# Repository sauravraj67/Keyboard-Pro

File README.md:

# Keyboard Pro

I built a 65% layout keyboard based on Seed Studio Xiao nrf52840 also It will have a 3.7v battery and an 0.91 inch OLED Screen. Switches will be HotSwapable. I used expander to connect the rows and coluns because there weren't enough pins available.  It is Bluetooth enabled  

## Features
-  nrf52840 Rp2040
- uses 65% Keyboard Layout 
-  Uses Keyboard Matrix
-  Had a rotor encoder and an 0.91 inch oled screen

  | Item | Price | Source |
|------|------:|--------|
| PCB + Shipping - Coupons | 25.14 | JLCPCB |
| KeyCaps | 15.04 | https://meckeys.com/shop/accessories/keyboard-accessories/keycaps/gengar-anime-keycap-set/ |
| Hot-swap (pack of 10) × 7 | 5.50 | https://meckeys.com/shop/accessories/keyboard-accessories/key-switches/kailh-hot-swap-socket/?attribute_pa_variations=white |
| Switches (pack of 10) × 7 | 22.10 | https://meckeys.com/shop/accessories/keyboard-accessories/key-switches/hmx-xinhai-switch/?attribute_pa_key-switches=hmx-xinhai-45g |
| Stabilizers | 10.76 | https://meckeys.com/shop/accessories/keyboard-accessories/more/glorious-goat-stabilizers/ |
| Meckeys Shipping | 1.10 | https://meckeys.com |
| Expander × 2 | 6.22 | https://robu.in/product/pca9555dwr-texas-instruments-400khz-soic-24-300mil-i-o-expanders-rohs/ |
| XIAO BLE nRF52840 | 12.40 | https://robu.in/product/seeed-studio-xiao-ble-nrf52840/ |
| On-Off Switch | 1.12 | https://robu.in/product/os202011ma0qn1-ck-100ma-dpdt-12v-10000-times-plugin-slide-switches-rohs/ |
| 2MΩ Resistor | 0.13 | https://robu.in/product/crcw12062m20fkea-vishay-smd-chip-resistor-2-2-mohm-%c2%b1-1-250-mw-1206-3216-metric-thick-film-general-purpose/ |
| 806kΩ Resistor | 0.13 | https://robu.in/product/rc0402fr-07806kl-yageo-smd-chip-resistor-806-kohm-%c2%b1-1-63-mw-0402-1005-metric-thick-film-general-purpose/ |
| Robu Shipping | 1.10 | https://robu.in |
| Solder Paste for SMD Components | 2.70 | https://www.amazon.in/gp/product/B0GY879KCL/ |
| 1N4148W-T4 Diodes (Pack of 15) × 5 ( used amazon beacuse wasn't avilable anywhere else)| 11.78 | https://www.amazon.in/gp/product/B0FZL2D1GG/ |
| **Total** | **115.22** | |

### Schematic<br><br>

## Made the Key-Matrix 
Hours- 5.5 hr <br>
So I opened the schematics and added a key switch and a diode. Then I had my way toward how many switches would be there per row . The number of keys per row wasn't constant So I made a rough sketch about how would I assign the columns and rows to each Key switch. after that as I would be using keyboard matrix ,so I needed to add a diode to each key switch to prevent ghosting. Then I started making the switch layout . I also kept in mind that each switches aren't of same length so I had to use specific footprints for each switches specifically as per the 65 % standard layout. The Switches will be hot-swapable as well. While making the switch matrix it was a bit time consuming as I tried to organized the switches as well as per there layout ,so that it will be easy for me to connect the wires.While reviewing I found a few placement and footprint mistakes so I solved them then I moved toward making the rows and columns connection and adding the labels to them So this is how it looks.

<br>

## Adding other components

Hours :- 2.5 hr <br>
So there is no footprint and symbol for the Xioa nRF52840 , So I downloaded them and added it to kicad also I knew that there weren't enough numbers of gpio pins on the Xiao nRF52840 so handle all the 15 columns and 5 rows So I needed to use an expander , So for that I used PCA9555D and read it's data sheet a bit , It will communicate to the MCU via I2C protocol , So I started adding the rows and columns label to it but even one expander wasn't enough So I had to add a second one to add the connections of all rows and columns then I did all the other connection on the expander.after that I added pins for Battery connection. the battery that we would be using will be of 3.7v lithium ion battery. and made a battery sense circuit. the nRF52840 has inbuild battery charging IC and it can control the charring part so I don't to add anything more after that I added a 4 pins for 0.91 inch oled display and added labels to it.after that I connected every label to the Xiao nRF52840. So this is how the final schematics look

###  PCB Design<br><br>

## Started with PCB ( Component placement)
Hours :- 4.75 hours <br>
SO I started with the hard part. Arranging the switches . I used a Grid of 19.05U so that the switches snap easily but that wasn't the case . I tried to snap them with each other via using different grid sizes and moving them then they use to snap properly. It look me a long time snapping the switches and overt to that placing switches at the right Place because each rows doesn't have same number of rows I had to align the first switch to the right place , also I added Stabilizers for any switch whose footprint was over 2.25U. The main thing was choosing the right Switch while placing and the most hectic thing was that switches don't use to snap directly . I have to move it around using different grid sizes to achieve the goal . Then I added the Xiao nRF52840 to the right top side a bit away from the corner then added the switches after that placed the Oled screen in the free space and added the expanders in places where there was free space I made few alteration of the keyboard but finally ended up with this after that I placed the diodes near to each respective switch to which it was attached onto the bottom layer of the PCB then I added the boundaries and this is how PCB layout looks now.

 ## Routed the PCB 
 Hours :- 6.5 <br>

 So I stated with routing the PCB I initially routed the diodes to the switches then I moved and started making rows and columns . I tried to make as clean routs as possible then I started routing the rows and columns to the expander . I used vias where there weren't space to rout . I had to make few alteration while routing so that my routs looks clean and workable . Many a times there weren't a way to rout . So I had to re-rout few traces but I was able to rout it to the two expanders. Then I stared connecting the SDA/SCL lines to the MCU from the expander and the OLED screen after that I made connection for the battery pins and battery connected circuit. So after all the rout the PCB looks like this with all the clean straight routs .

###  Made and Polished the Case <br><br>
Hours :- 5.75 hours 

So I took the measurements of the keyboard then made a sketch of same size.after that I added 1 mm releat from each side and added a boundary sketch and curved it edges.after that I need to add sketches for holding the plates . So I added it's boundary and started making symmetric Rectangles and circles for holding the Plate boundary , I repeted it for the tob and bottom<br>then to the sides<br> <br>after that I made a simple base then extruded it as per the needs to make the base Case basic design all the meserments were pre calculated.
after that I added PCB aligned it perfectly with the sketch then moved it to a calculated height ( this time the calculations things were right).then I added the 3D model of the MCU and started making holes on the Case for the USB-C for that I used a simple sketch and extruded to to make a cut
 then made the middle and the top layer 

And polished the case and these are the final result

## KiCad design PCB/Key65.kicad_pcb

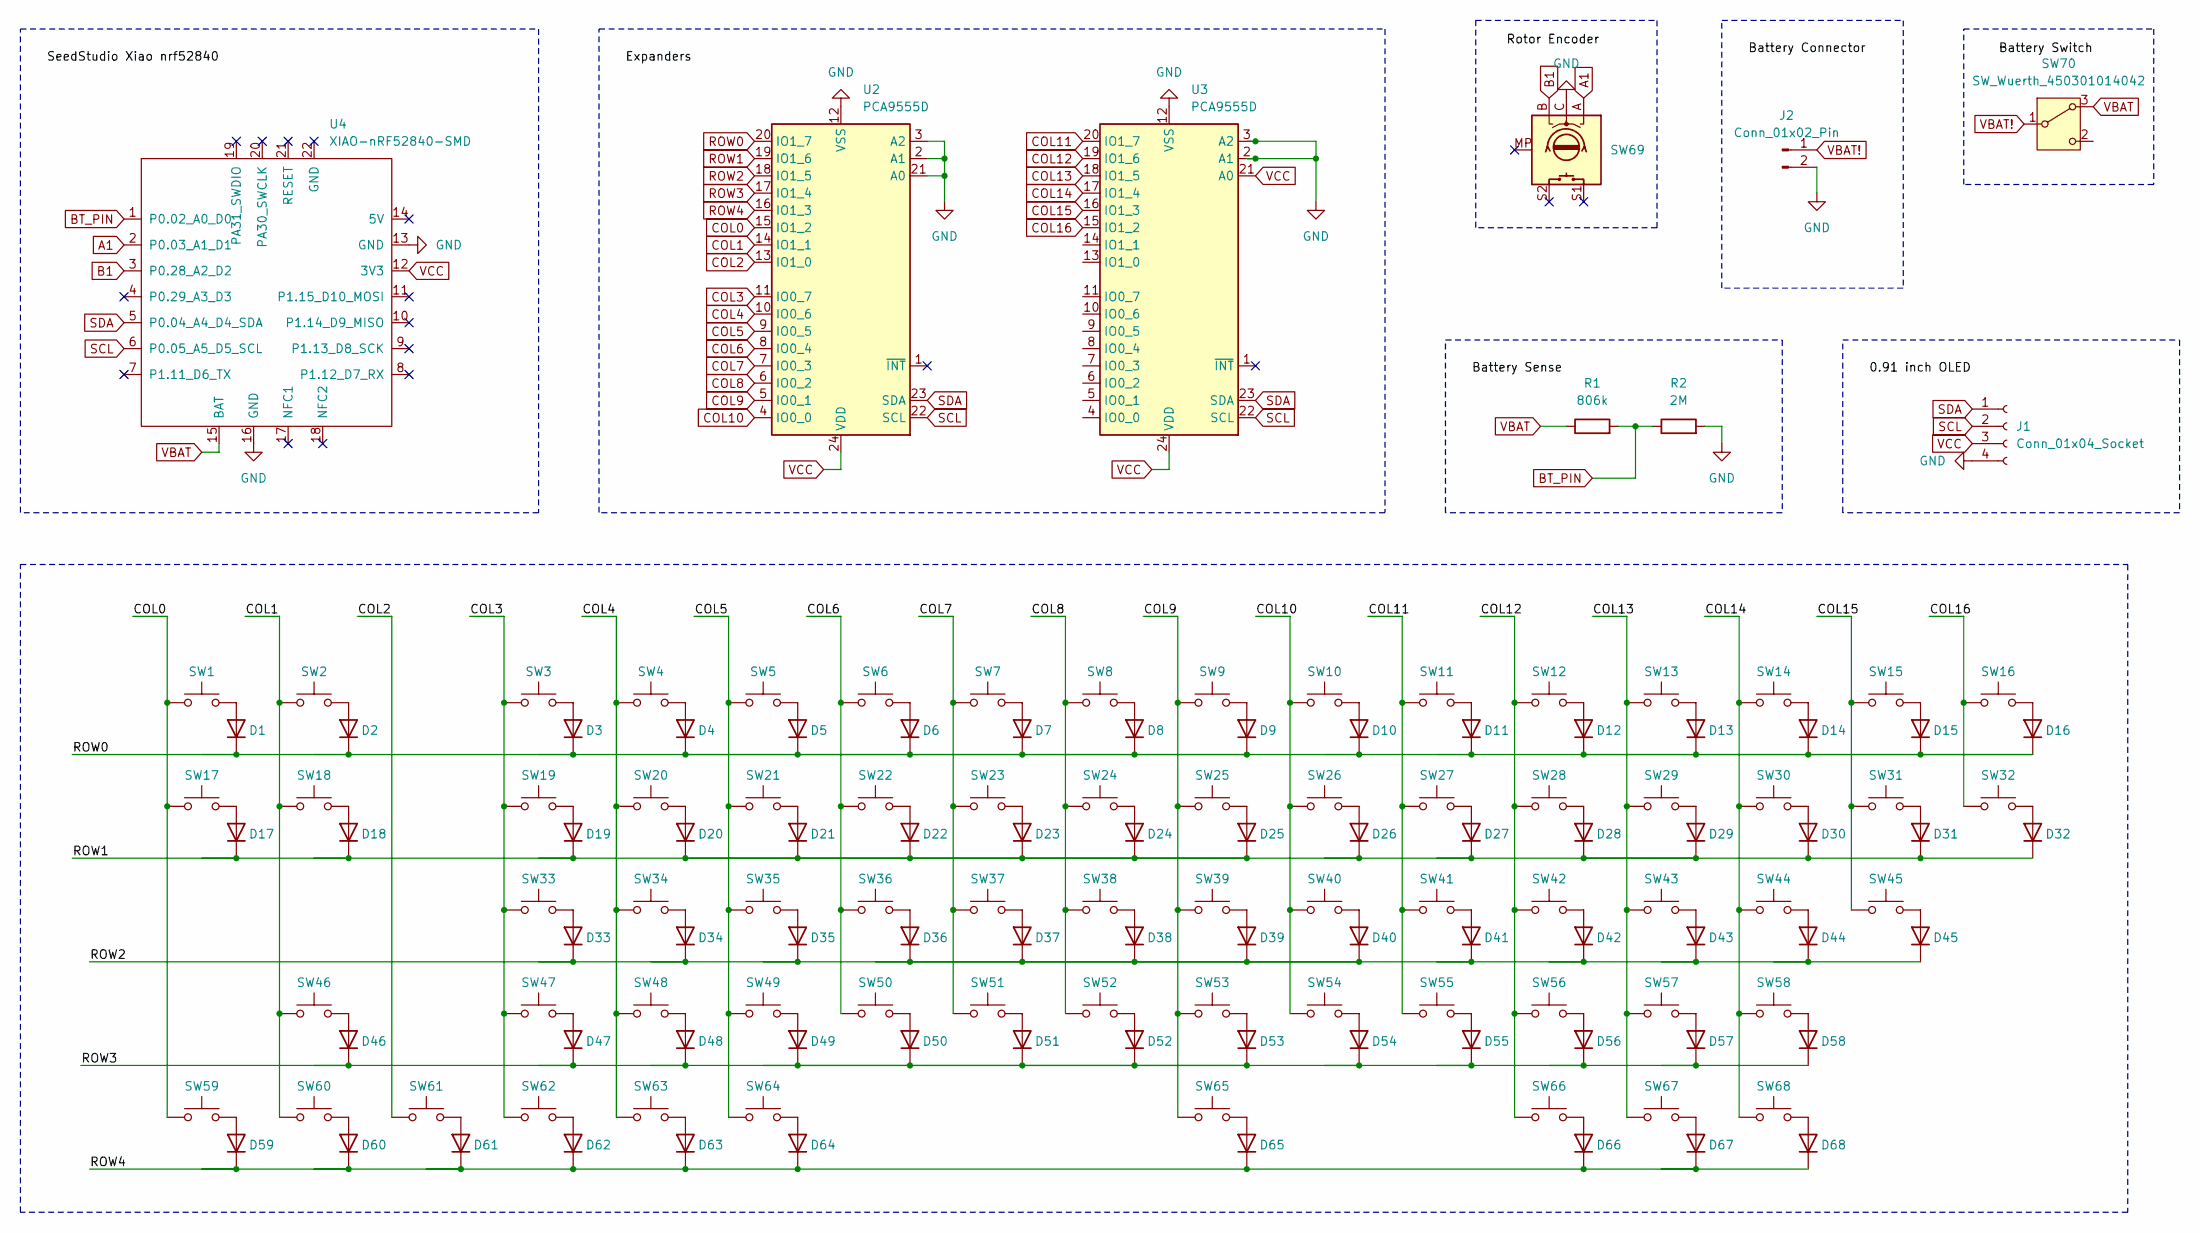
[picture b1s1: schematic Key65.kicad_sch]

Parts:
D1, D2, D3, D4, D5, D6, D7, D8, D9, D10, D11, D12, D13, D14, D15, D16, D17, D18, D19, D20, D21, D22, D23, D24, D25, D26, D27, D28, D29, D30, D31, D32, D33, D34, D35, D36, D37, D38, D39, D40, D41, D42, D43, D44, D45, D46, D47, D48, D49, D50, D51, D52, D53, D54, D55, D56, D57, D58, D59, D60, D61, D62, D63, D64, D65, D66, D67, D68: D; D_SOD-123
J1: Conn_01x04_Socket; PinHeader_1x04_P2.54mm_Vertical
J2: Conn_01x02_Pin; JST_JWPF_B02B-JWPF-SK-R_1x02_P2.00mm_Vertical
R1: 806k; R_0805_2012Metric
R2: 2M; R_0805_2012Metric
SW1, SW2, SW3, SW4, SW5, SW6, SW7, SW8, SW9, SW10, SW11, SW12, SW13, SW14, SW15, SW16, SW17, SW18, SW19, SW20, SW21, SW22, SW23, SW24, SW25, SW26, SW27, SW28, SW29, SW30, SW31, SW32, SW33, SW34, SW35, SW36, SW37, SW38, SW39, SW40, SW41, SW42, SW43, SW44, SW45, SW46, SW47, SW48, SW49, SW50, SW51, SW52, SW53, SW54, SW55, SW56, SW57, SW58, SW59, SW60, SW61, SW62, SW63, SW64, SW65, SW66, SW67, SW68: SW_Push; SW_MX_HS_CPG151101S11_1u
SW69: RotaryEncoder_Switch_MP; RotaryEncoder_Alps_EC11E-Switch_Vertical_H20mm
SW70: SW_Wuerth_450301014042; SW_Slide_SPDT_Straight_CK_OS102011MS2Q
U2, U3: PCA9555D; SOIC-24W_7.5x15.4mm_P1.27mm
U4: XIAO-nRF52840-SMD; modified-XIAO-nRF52840-SMD

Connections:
A1: SW69.A, U4.2 (P0.03_A1_D1)
B1: SW69.B, U4.3 (P0.28_A2_D2)
BT_PIN: R1.2, R2.1, U4.1 (P0.02_A0_D0)
COL0: SW1.1, SW17.1, SW59.1, U2.15 (IO1_2)
COL1: SW2.1, SW18.1, SW46.1, SW60.1, U2.14 (IO1_1)
COL2: SW61.1, U2.13 (IO1_0)
COL3: SW3.1, SW19.1, SW33.1, SW47.1, SW62.1, U2.11 (IO0_7)
COL4: SW4.1, SW20.1, SW34.1, SW48.1, SW63.1, U2.10 (IO0_6)
COL5: SW5.1, SW21.1, SW35.1, SW49.1, SW64.1, U2.9 (IO0_5)
COL6: SW6.1, SW22.1, SW36.1, SW50.1, U2.8 (IO0_4)
COL7: SW7.1, SW23.1, SW37.1, SW51.1, U2.7 (IO0_3)
COL8: SW8.1, SW24.1, SW38.1, SW52.1, U2.6 (IO0_2)
COL9: SW9.1, SW25.1, SW39.1, SW53.1, SW65.1, U2.5 (IO0_1)
COL10: SW10.1, SW26.1, SW40.1, SW54.1, U2.4 (IO0_0)
COL11: SW11.1, SW27.1, SW41.1, SW55.1, U3.20 (IO1_7)
COL12: SW12.1, SW28.1, SW42.1, SW56.1, SW66.1, U3.19 (IO1_6)
COL13: SW13.1, SW29.1, SW43.1, SW57.1, SW67.1, U3.18 (IO1_5)
COL14: SW14.1, SW30.1, SW44.1, SW58.1, SW68.1, U3.17 (IO1_4)
COL15: SW15.1, SW31.1, SW45.1, U3.16 (IO1_3)
COL16: SW16.1, SW32.1, U3.15 (IO1_2)
GND: J1.4, J2.2, R2.2, SW69.C, U2.2 (A1), U2.3 (A2), U2.12 (VSS), U2.21 (A0), U3.2 (A1), U3.3 (A2), U3.12 (VSS), U4.13 (GND), U4.16 (GND)
unnamed: D1.2 (A), SW1.2
unnamed: D2.2 (A), SW2.2
unnamed: D3.2 (A), SW3.2
unnamed: D4.2 (A), SW4.2
unnamed: D5.2 (A), SW5.2
unnamed: D6.2 (A), SW6.2
unnamed: D7.2 (A), SW7.2
unnamed: D8.2 (A), SW8.2
unnamed: D9.2 (A), SW9.2
unnamed: D10.2 (A), SW10.2
unnamed: D11.2 (A), SW11.2
unnamed: D12.2 (A), SW12.2
unnamed: D13.2 (A), SW13.2
unnamed: D14.2 (A), SW14.2
unnamed: D15.2 (A), SW15.2
unnamed: D16.2 (A), SW16.2
unnamed: D17.2 (A), SW17.2
unnamed: D18.2 (A), SW18.2
unnamed: D19.2 (A), SW19.2
unnamed: D20.2 (A), SW20.2
unnamed: D21.2 (A), SW21.2
unnamed: D22.2 (A), SW22.2
unnamed: D23.2 (A), SW23.2
unnamed: D24.2 (A), SW24.2
unnamed: D25.2 (A), SW25.2
unnamed: D26.2 (A), SW26.2
unnamed: D27.2 (A), SW27.2
unnamed: D28.2 (A), SW28.2
unnamed: D29.2 (A), SW29.2
unnamed: D30.2 (A), SW30.2
unnamed: D31.2 (A), SW31.2
unnamed: D32.2 (A), SW32.2
unnamed: D33.2 (A), SW33.2
unnamed: D34.2 (A), SW34.2
unnamed: D35.2 (A), SW35.2
unnamed: D36.2 (A), SW36.2
unnamed: D37.2 (A), SW37.2
unnamed: D38.2 (A), SW38.2
unnamed: D39.2 (A), SW39.2
unnamed: D40.2 (A), SW40.2
unnamed: D41.2 (A), SW41.2
unnamed: D42.2 (A), SW42.2
unnamed: D43.2 (A), SW43.2
unnamed: D44.2 (A), SW44.2
unnamed: D45.2 (A), SW45.2
unnamed: D46.2 (A), SW46.2
unnamed: D47.2 (A), SW47.2
unnamed: D48.2 (A), SW48.2
unnamed: D49.2 (A), SW49.2
unnamed: D50.2 (A), SW50.2
unnamed: D51.2 (A), SW51.2
unnamed: D52.2 (A), SW52.2
unnamed: D53.2 (A), SW53.2
unnamed: D54.2 (A), SW54.2
unnamed: D55.2 (A), SW55.2
unnamed: D56.2 (A), SW56.2
unnamed: D57.2 (A), SW57.2
unnamed: D58.2 (A), SW58.2
unnamed: D59.2 (A), SW59.2
unnamed: D60.2 (A), SW60.2
unnamed: D61.2 (A), SW61.2
unnamed: D62.2 (A), SW62.2
unnamed: D63.2 (A), SW63.2
unnamed: D64.2 (A), SW64.2
unnamed: D65.2 (A), SW65.2
unnamed: D66.2 (A), SW66.2
unnamed: D67.2 (A), SW67.2
unnamed: D68.2 (A), SW68.2
ROW0: D1.1 (K), D2.1 (K), D3.1 (K), D4.1 (K), D5.1 (K), D6.1 (K), D7.1 (K), D8.1 (K), D9.1 (K), D10.1 (K), D11.1 (K), D12.1 (K), D13.1 (K), D14.1 (K), D15.1 (K), D16.1 (K), U2.20 (IO1_7)
ROW1: D17.1 (K), D18.1 (K), D19.1 (K), D20.1 (K), D21.1 (K), D22.1 (K), D23.1 (K), D24.1 (K), D25.1 (K), D26.1 (K), D27.1 (K), D28.1 (K), D29.1 (K), D30.1 (K), D31.1 (K), D32.1 (K), U2.19 (IO1_6)
ROW2: D33.1 (K), D34.1 (K), D35.1 (K), D36.1 (K), D37.1 (K), D38.1 (K), D39.1 (K), D40.1 (K), D41.1 (K), D42.1 (K), D43.1 (K), D44.1 (K), D45.1 (K), U2.18 (IO1_5)
ROW3: D46.1 (K), D47.1 (K), D48.1 (K), D49.1 (K), D50.1 (K), D51.1 (K), D52.1 (K), D53.1 (K), D54.1 (K), D55.1 (K), D56.1 (K), D57.1 (K), D58.1 (K), U2.17 (IO1_4)
ROW4: D59.1 (K), D60.1 (K), D61.1 (K), D62.1 (K), D63.1 (K), D64.1 (K), D65.1 (K), D66.1 (K), D67.1 (K), D68.1 (K), U2.16 (IO1_3)
SCL: J1.2, U2.22 (SCL), U3.22 (SCL), U4.6 (P0.05_A5_D5_SCL)
SDA: J1.1, U2.23 (SDA), U3.23 (SDA), U4.5 (P0.04_A4_D4_SDA)
VBAT: R1.1, SW70.3 (A), U4.15 (BAT)
VBAT!: J2.1, SW70.1 (B)
VCC: J1.3, U2.24 (VDD), U3.21 (A0), U3.24 (VDD), U4.12 (3V3)

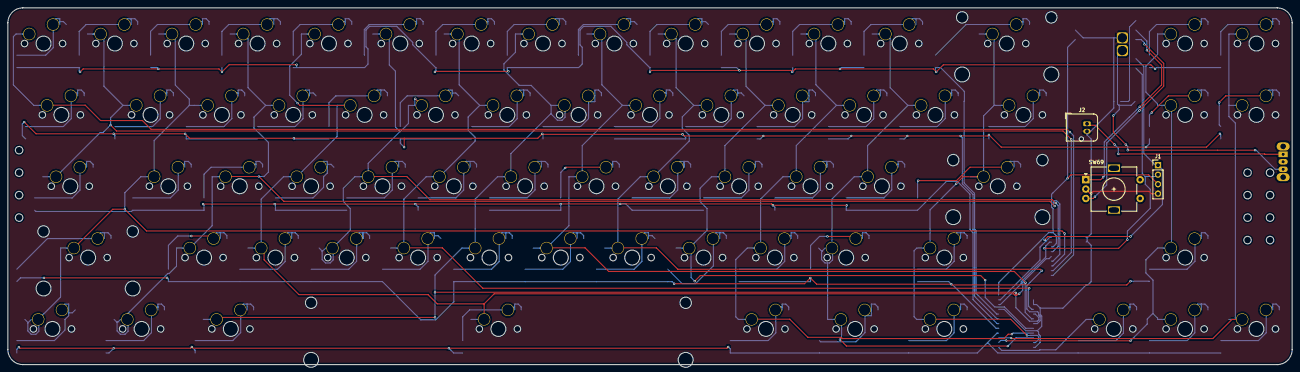
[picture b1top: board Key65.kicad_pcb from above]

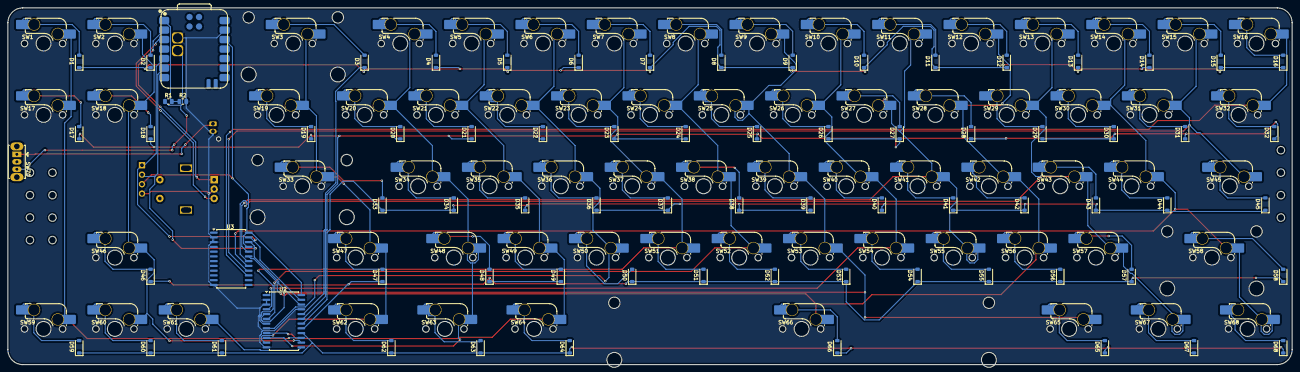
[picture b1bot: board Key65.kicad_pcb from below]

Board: 2 copper layers, 342.9 x 95.2 mm, 149 parts (142 on the bottom side), 99 nets.

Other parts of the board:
S1: STAB_MX_2u
S2, S3: STAB_MX_2.25u
S4: STAB_MX_6.25u
